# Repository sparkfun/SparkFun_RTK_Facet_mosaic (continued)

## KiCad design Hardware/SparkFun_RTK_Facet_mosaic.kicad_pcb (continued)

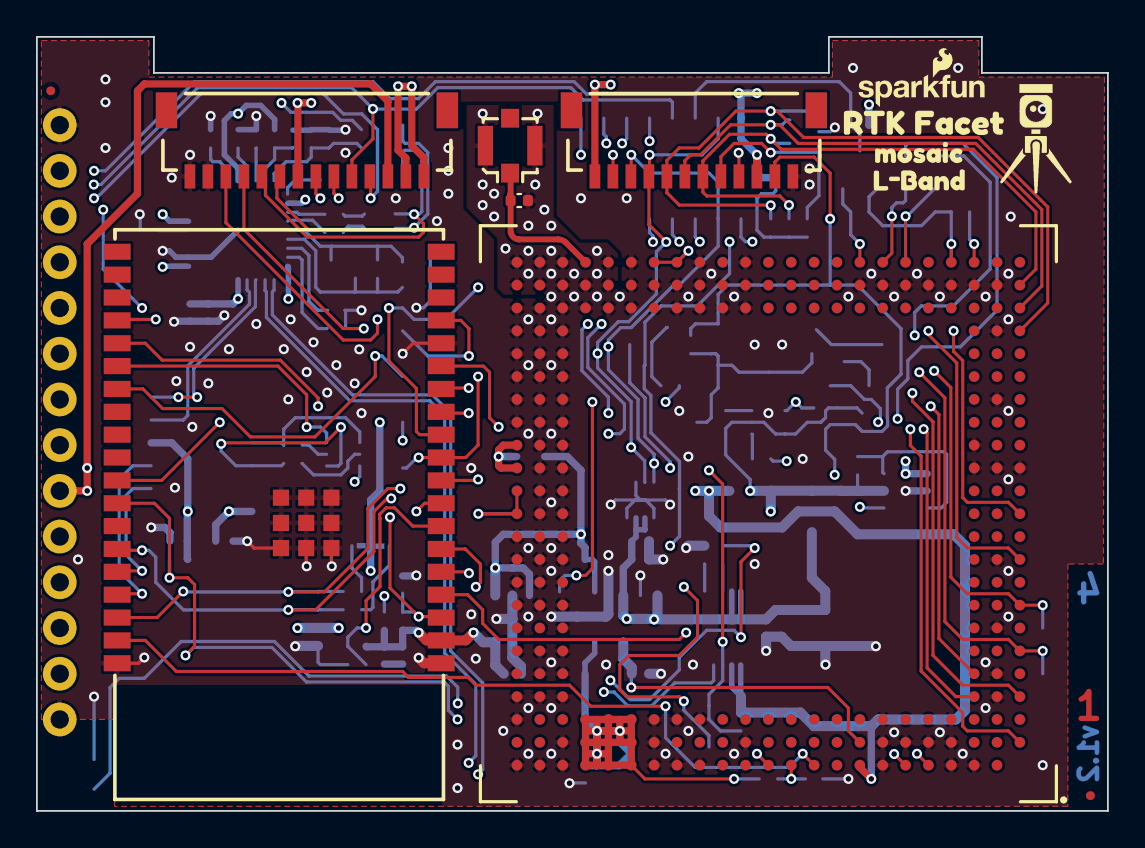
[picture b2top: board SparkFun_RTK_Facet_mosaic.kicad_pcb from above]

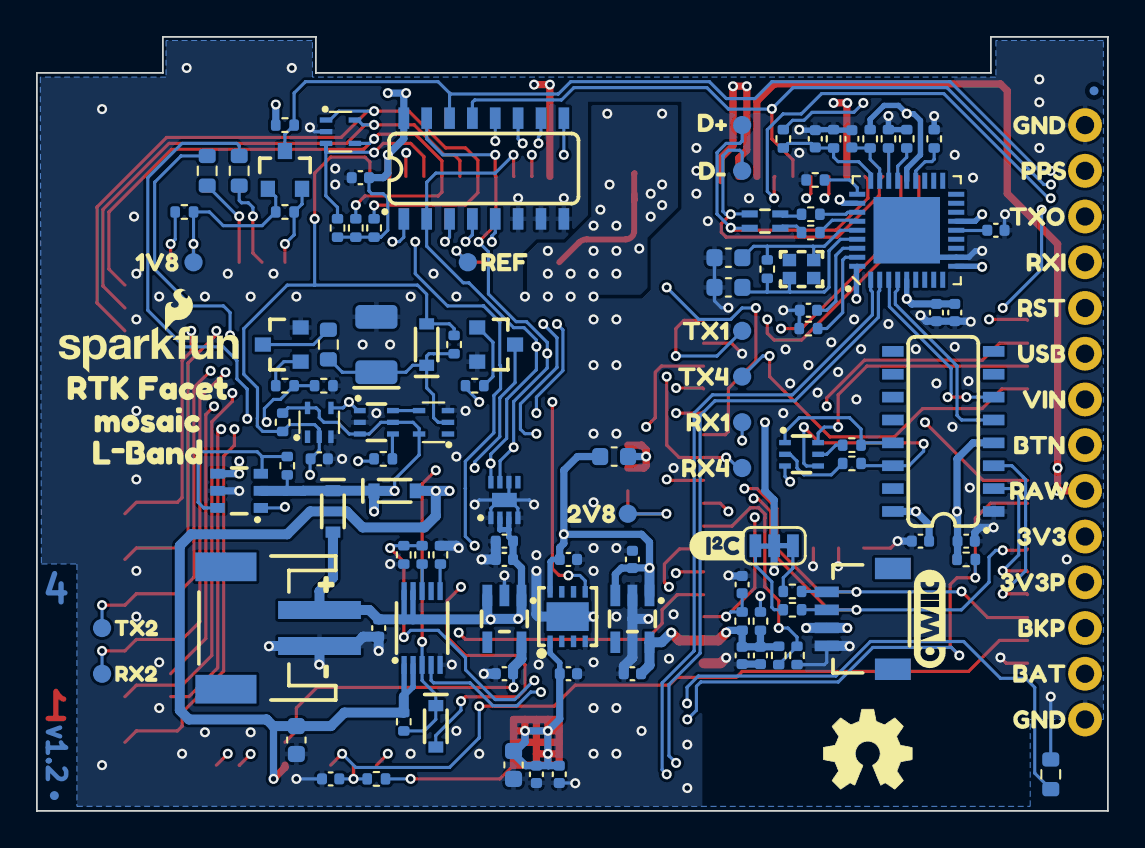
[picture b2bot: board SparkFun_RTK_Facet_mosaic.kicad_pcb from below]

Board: 4 copper layers, 59.5 x 43.0 mm, 170 parts (143 on the bottom side), 95 nets.

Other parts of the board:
C8: 1.0uF; C_0402_1005Metric
R6: 2.2k; R_0402_1005Metric
Ref**: Val**; SparkFun_RTK_15mm
Ref**#2: Val**; OSHW_Logo_5mm
kibuzzard-65A7F4BF: G***; kibuzzard-65A7F4BF
kibuzzard-65A7F4D6: G***; kibuzzard-65A7F4D6
kibuzzard-65A7F4E8: G***; kibuzzard-65A7F4E8
kibuzzard-65A7F5A7: G***; kibuzzard-65A7F5A7
kibuzzard-65A7F5BC: G***; kibuzzard-65A7F5BC
kibuzzard-65A7F5CF: G***; kibuzzard-65A7F5CF
kibuzzard-65A7F5E3: G***; kibuzzard-65A7F5E3
kibuzzard-65A7F7BA: G***; kibuzzard-65A7F7BA
kibuzzard-65A7F7EA: G***; kibuzzard-65A7F7EA
kibuzzard-65A7F47C: G***; kibuzzard-65A7F47C
kibuzzard-65A7F60E: G***; kibuzzard-65A7F60E
kibuzzard-65A7F63F: G***; kibuzzard-65A7F63F
kibuzzard-65A7F440, kibuzzard-65A7F440#2: G***; kibuzzard-65A7F440
kibuzzard-65A7F499: G***; kibuzzard-65A7F499
kibuzzard-65A7F511: G***; kibuzzard-65A7F511
kibuzzard-65A7F548: G***; kibuzzard-65A7F548
kibuzzard-65A7F565: G***; kibuzzard-65A7F565
kibuzzard-65A7F574: G***; kibuzzard-65A7F574
kibuzzard-65A7F686: G***; kibuzzard-65A7F686
kibuzzard-65A7F697: G***; kibuzzard-65A7F697
kibuzzard-65A7F771: G***; kibuzzard-65A7F771
kibuzzard-65A7F891: G***; kibuzzard-65A7F891
kibuzzard-65AEA1E6: G***; kibuzzard-65AEA1E6
kibuzzard-65AEA201: G***; kibuzzard-65AEA201
kibuzzard-65AEA759: G***; kibuzzard-65AEA759
kibuzzard-670CFFCD: G***; kibuzzard-670CFFCD
kibuzzard-670CFFE9: G***; kibuzzard-670CFFE9
kibuzzard-65776CFF, kibuzzard-65776CFF#2: G***; kibuzzard-65776CFF
kibuzzard-65776D0F: G***; kibuzzard-65776D0F
kibuzzard-65776D09: G***; kibuzzard-65776D09
kibuzzard-65777033: G***; kibuzzard-65777033
kibuzzard-65777037: G***; kibuzzard-65777037

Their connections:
GND: C8.2; also elsewhere on the board

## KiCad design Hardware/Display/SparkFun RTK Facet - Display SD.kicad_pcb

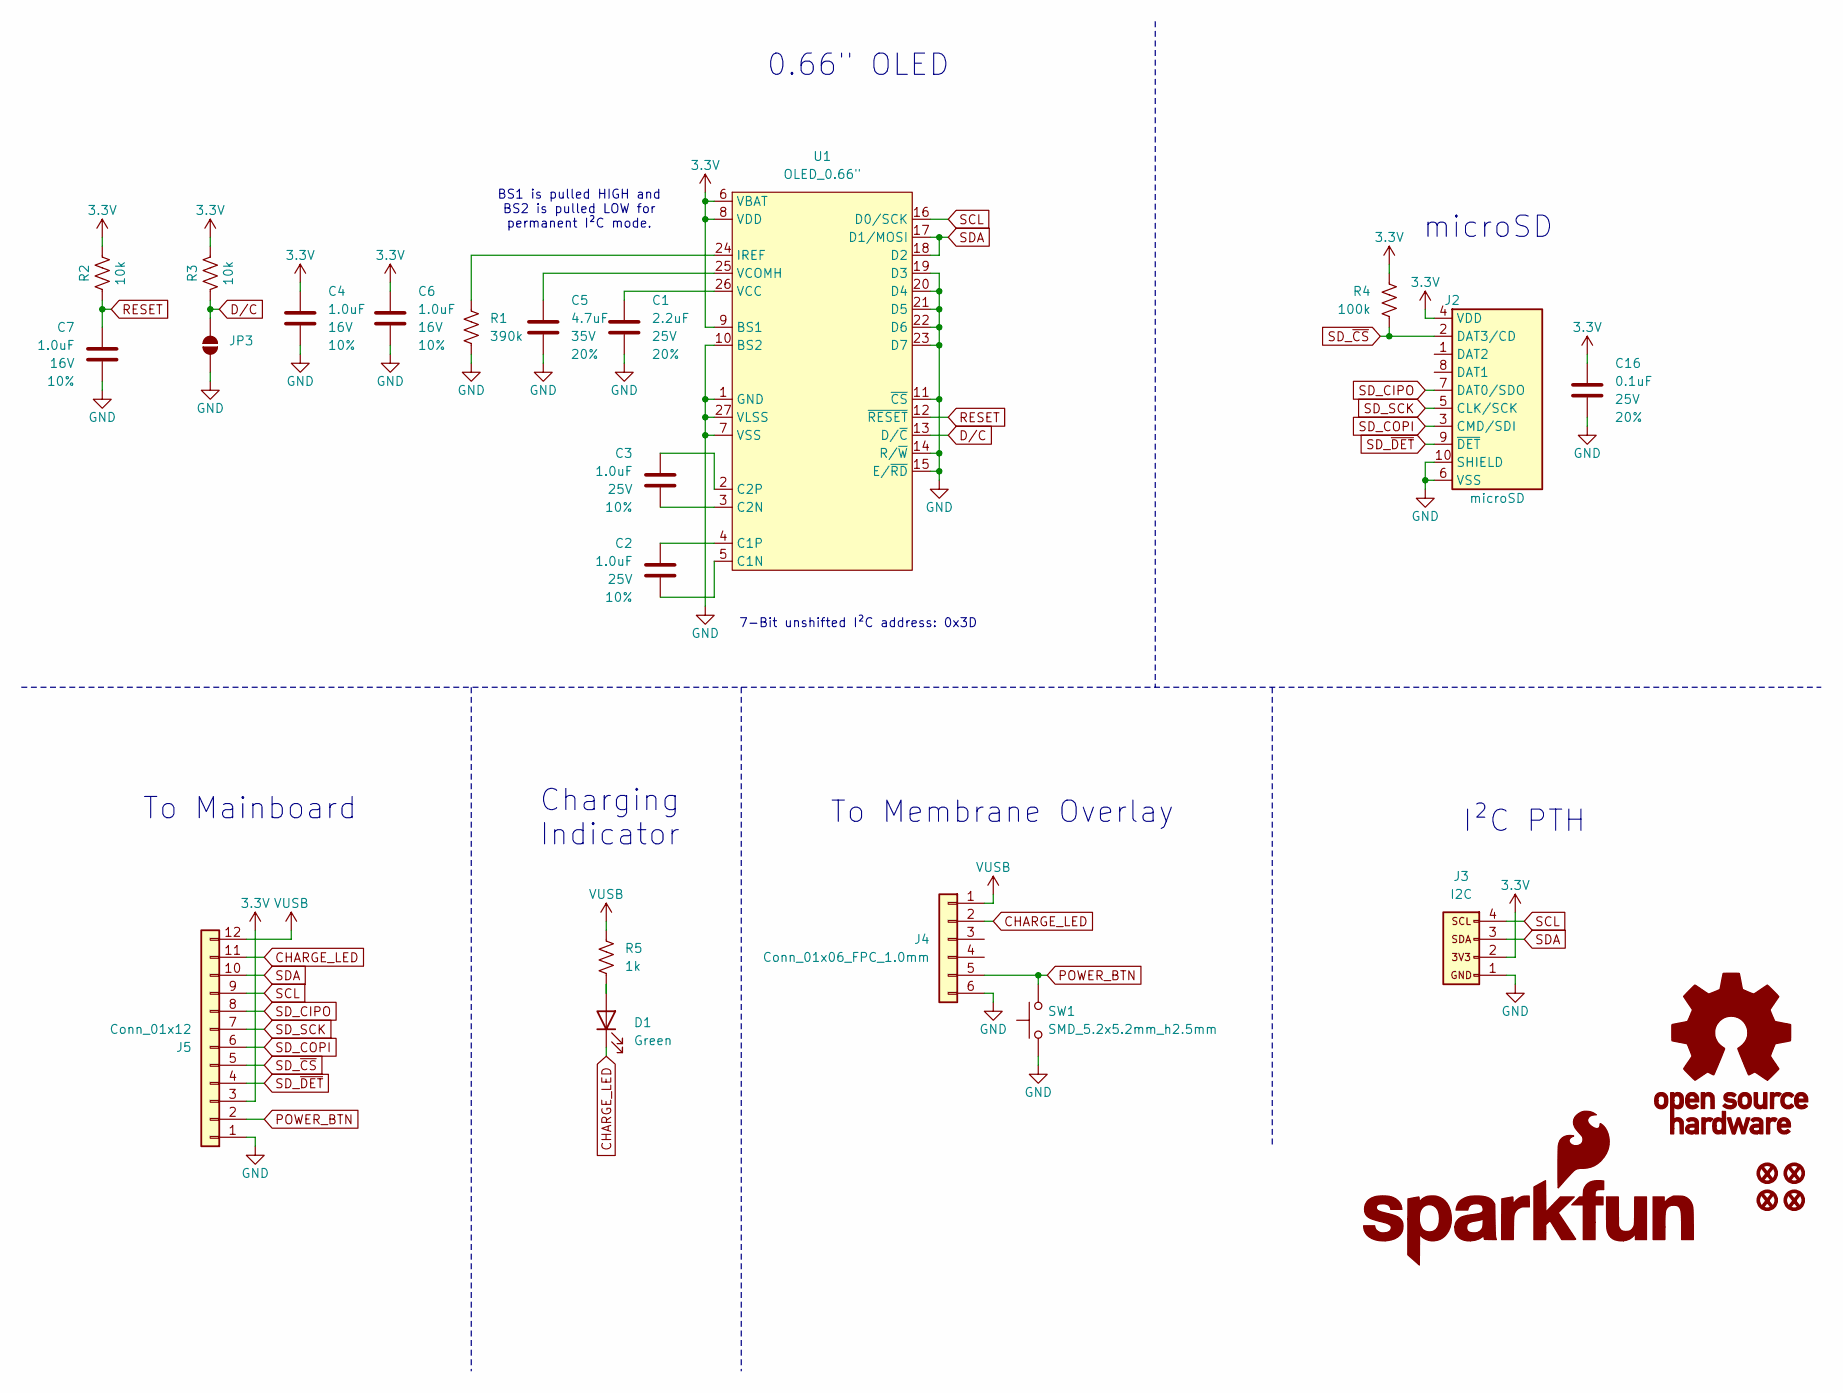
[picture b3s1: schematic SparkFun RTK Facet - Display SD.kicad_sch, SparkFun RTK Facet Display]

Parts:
C1: 2.2uF; C_0805_2012Metric; Voltage 25V; Tolerance 20%
C2, C3: 1.0uF; C_0805_2012Metric; Voltage 25V; Tolerance 10%
C4, C6, C7: 1.0uF; C_0603_1608Metric; Voltage 16V; Tolerance 10%
C5: 4.7uF; C_0603_1608Metric; Voltage 35V; Tolerance 20%
C16: 0.1uF; C_0603_1608Metric; Voltage 25V; Tolerance 20%
D1: Green; LED_1206_Bottom_Green
FID1, FID2, FID3, FID4: Fiducial_0.5mm; Fiducial_0.5mm_Mask1mm
G1: SparkFun_Logo
G2: OSHW_Logo; Creative_Commons_License
J2: microSD; microSD_External_Pin
J3: I2C; 1x04
J4: Conn_01x06_FPC_1.0mm; FPC_1.0mm-6_LIF
J5: Conn_01x12; JST_SMD_1.0mm-12_RA
JP3: Jumper_2_NO
R1: 390k; R_0603_1608Metric
R2, R3: 10k; R_0603_1608Metric
R4: 100k; R_0603_1608Metric
R5: 1k; R_0402_1005Metric
SW1: SMD_5.2x5.2mm_h2.5mm; Push_SMD_5.2x5.2mm_h2.5mm
U1: OLED_0.66"; OLED_0.66-SMD

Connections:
3.3V: C4.1, C6.1, C16.1, J2.4 (VDD), J3.2, J5.3, R2.2, R3.1, R4.1, U1.6 (VBAT), U1.8 (VDD), U1.9 (BS1)
CHARGE_LED: D1.1 (K), J4.2, J5.11
D/C: JP3.2 (B), R3.2, U1.13 (D/~C)
GND: C1.2, C4.2, C5.2, C6.2, C7.2, C16.2, J2.6 (VSS), J2.10 (SHIELD), J3.1, J4.6, J5.1, JP3.1 (A), R1.2, SW1.1, U1.1 (GND), U1.7 (VSS), U1.10 (BS2), U1.11 (~CS), U1.14 (R/~W), U1.15 (E/~RD), U1.19 (D3), U1.20 (D4), U1.21 (D5), U1.22 (D6), U1.23 (D7), U1.27 (VLSS), U1.28 (GND)
unnamed: D1.2 (A), R5.2
unnamed: C2.2, U1.5 (C1N)
unnamed: C2.1, U1.4 (C1P)
unnamed: C3.2, U1.3 (C2N)
unnamed: C3.1, U1.2 (C2P)
unnamed: R1.1, U1.24 (IREF)
unnamed: C1.1, U1.26 (VCC)
unnamed: C5.1, U1.25 (VCOMH)
POWER_BTN: J4.5, J5.2, SW1.2
RESET: C7.1, R2.1, U1.12 (~RESET)
SCL: J3.4, J5.9, U1.16 (D0/SCK)
SDA: J3.3, J5.10, U1.17 (D1/MOSI), U1.18 (D2)
SD_CIPO: J2.7 (DAT0/SDO), J5.8
SD_COPI: J2.3 (CMD/SDI), J5.6
SD_SCK: J2.5 (CLK/SCK), J5.7
SD_~CS: J2.2 (DAT3/CD), J5.5, R4.2
SD_~DET: J2.9 (~DET), J5.4
VUSB: J4.1, J5.12, R5.1

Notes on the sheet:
7-Bit unshifted I²C address: 0x3D
BS1 is pulled HIGH and BS2 is pulled LOW for permanent I²C mode.
0.66" OLED
To Membrane Overlay
I²C PTH
To Mainboard
Charging Indicator
microSD

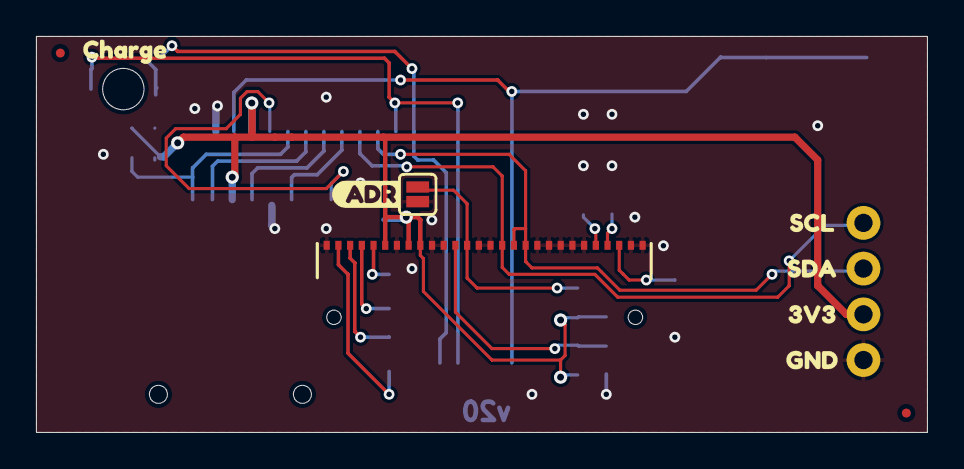
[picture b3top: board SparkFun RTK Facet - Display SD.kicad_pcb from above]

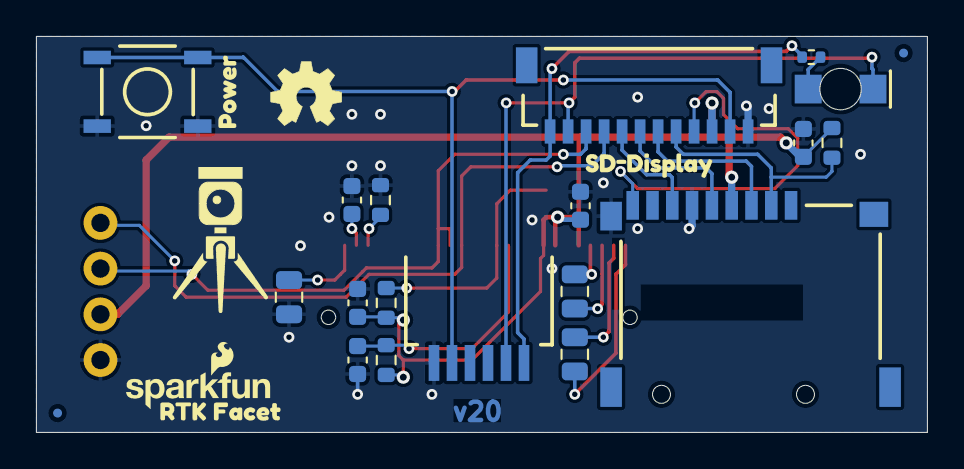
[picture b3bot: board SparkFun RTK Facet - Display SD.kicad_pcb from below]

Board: 2 copper layers, 49.5 x 22.0 mm, 37 parts (26 on the bottom side), 22 nets.

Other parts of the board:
Ref**: Val**; SparkFun_RTK_20mm
Ref**#2: Val**; OSHW_Logo_4mm
kibuzzard-66E8FA3C: G***; kibuzzard-66E8FA3C
kibuzzard-66E8FA6A: G***; kibuzzard-66E8FA6A
kibuzzard-66E8FA6F: G***; kibuzzard-66E8FA6F
kibuzzard-66E8FA7A: G***; kibuzzard-66E8FA7A
kibuzzard-66E8FA21: G***; kibuzzard-66E8FA21
kibuzzard-66E8FA52: G***; kibuzzard-66E8FA52
kibuzzard-66E8FA75: G***; kibuzzard-66E8FA75
kibuzzard-66E8FB1B: G***; kibuzzard-66E8FB1B
kibuzzard-66E8FB47: G***; kibuzzard-66E8FB47

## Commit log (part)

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2024-01-11 Schematic updates
2024-01-15 Ready for airwire review
2024-01-16 Work in progress...
2024-01-17 Routed
2024-01-17 With Buzzard text
2024-01-17 Nudge things on USB schematic
2024-01-18 Do over with RSP32 Pico Mini - routed
2024-01-18 Switching back to the WROVER - routed
2024-01-19 Add route out text
2024-01-19 Update schematic - rotate pages
2024-01-22 Panelized with corrected FPC paste
2024-01-22 Add missing PROD_IDs
2024-01-22 Panelize with missing PROD_IDs
2024-01-22 Add missing PROD_ID
2024-01-22 Add extra Test Points
2024-01-23 Final tweaks
2024-01-23 Add RFCMF1220100M4T value
2024-01-23 Update datasheets
2024-03-06 Pull up unused TX pins, just in case
2024-05-01 v1.1 routed
2024-05-02 V1.1 Panelized
2024-05-03 v1.1 Final Polish
2024-08-21 Update 3D models
2024-10-08 v1.2 routed
2024-10-08 v1.2 Panelized
2024-10-14 Add SD_DET and 1A regulator
2024-10-15 Add JST PROD_IDs. Update AP7361C regulator
2024-12-20 Update test sketches
2025-02-14 Add display and connector boards
2025-02-14 Add README and LICENSE
2025-02-21 Initial documentation draft
    Files to generate product documentation on GitHub pages
2025-02-21 Use SparkPNT
    Replace instances of SparkFun with SparkPNT
2025-02-21 Update README.md
    Fix typos
    Replace product "redirect" link with "magento" link
2025-02-21 Add katex support
    Leaving feature disabled due to issues
2025-02-21 Update extra.css
    Fix indentation (tabs vs spaces)
2025-02-21 Add generator feature
    Adds feature to shift generator to right side of footer
2025-02-21 Update mkdocs.yml
    Fix typos
    Add discourse link
    Exclude glossary from build
2025-02-21 Add glossary files
2025-02-21 Rename file
2025-02-21 Add workflow to build documentation
2025-02-21 Deployed 4bd92c5 with MkDocs version: 1.6.1
2025-02-21 Fix typos
2025-02-21 Rename file
    Change `gnss_board` and `primary_board` to `main_board`
2025-02-21 Add board files
    Add schematics for display and connector boards
    Rework file links
2025-02-21 Update product info
    Update links and name for the hardcase
2025-02-21 Update troubleshooting_tips.md
    Add replacement parts
2025-02-21 Deployed 22fa7c5 with MkDocs version: 1.6.1
2025-02-21 Update supported messages
2025-02-21 Deployed bcba3fe with MkDocs version: 1.6.1
2025-02-21 Fix photos
2025-02-21 Link firmware manual
    Hyphenate open-source
    Link in Firmware manual
    Move Facet tutorial lower in list
2025-02-21 Use hookup guide
    Replace "product manual" with "hookup guide"
2025-02-21 Deployed 02d8ff4 with MkDocs version: 1.6.1
2025-02-24 Replace icon
2025-02-24 Deployed 732e5bd with MkDocs version: 1.6.1
2025-02-25 Correct RADIO img. Add COM port names
2025-02-25 Deployed 2c3fa87 with MkDocs version: 1.6.1
2025-02-25 Correct default baud rate
2025-02-25 Deployed 3e9232b with MkDocs version: 1.6.1
2025-02-25 Move annotation
2025-02-25 Deployed 0a2b792 with MkDocs version: 1.6.1
2025-07-23 Update docs to remove L-Band from product name
2025-07-23 Deployed d4c4a5b with MkDocs version: 1.6.1
2025-07-23 Update docs to remove L-Band
2025-07-23 Deployed 7bf15e1 with MkDocs version: 1.6.1
2025-09-11 Remove git-authors
2025-09-11 Deployed c26f8e2 with MkDocs version: 1.6.1
2025-09-11 Deployed 7f0c315 with MkDocs version: 1.6.1
2025-09-12 Update component documentation
    Updates the firmware, datasheet, and manuals for the mosaic-X5
2025-09-12 Update footprints
    Updates the 3D model file path for the footprints
2025-09-12 Update .gitignore
    Remove leftover merge conflict markers
    Consolidate duplicate entries
    Removes ignored file types
2025-09-15 Replace <center> tag
    Update <center> tags to conform to HTML5 standards
2026-06-03 Deployed 841defd with MkDocs version: 1.6.1
